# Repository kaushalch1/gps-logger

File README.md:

# gps Logger

## About the Project

this is a gps device designed to record and track journeys without depending on a phone or a constant bluetooth connection.the idea behind this project is to make it easier to collect travel and movement data while hiking or cycling or exploring new places.

the device uses an esp-s3 as its main controller, along with a gps receiver and an oled display, a motion sensor, and a microsd card for storing data. it records information locally so that it can be accessed later, even without an internet connection.

## Tools used

kicad ,github
## how to build it
Step 1 — Solder passive components
Step 2 — Install the ESP32-S3
Step 3 — Install the GPS module
Step 4 — Install the OLED and IMU
Step 5 — Install the microSD socket and controls
Step 6 — Complete power circuitry
St3ep 7-Flash your firmware
## How It Works

When the pcb starts, it initializes the display, gps receiver, microSD card, motion sensor, and bluetooth. The display provides an overview of the device's current status.

When recording starts, the device creates a csv file on the microsd card. It periodically saves available gps information and motion sensor readings to that file.

Bluetooth allows commands to be sent to the device and recorded logs to be requested and since the data is stored locally, recording does not require an active bluetooth connection.
## Features

- GPS Tracking: Collects location, speed, altitude, and time information from the GPS receiver.
- offline logging: Saves gps and sensor readings to a microsd card in csv format without needing a phone or Bluetooth connection.
- OLED display: shows gps status, speed, battery voltage, and recording status.
- Motion sensing: Uses the bmi270 accelerometer and gyroscope to collect movement data.
- Bluetooth connectivity: allows a compatible phone or computer to communicate with the device and request recorded logs.
- Physical controls: includes buttons for starting or stopping recordings and marking waypoints, and switching display pages.
- Status indicators: Uses an led and buzzer to provide basic feedback during operation.
# GPS Logger — Bill of Materials

| Name | Purpose | Quantity | Total Cost (USD) | Link | Distributor |
|---|---|---:|---:|---|---|
| ESP32-S3-WROOM-1-N16R8 | Main MCU (Wi-Fi/BLE) | 1 | 5.54 | [Link](https://www.lcsc.com/product-detail/C2913202.html) | LCSC |
| NEO-M9N-00B | GNSS receiver | 1 | 16.41 | [Link](https://www.lcsc.com/product-detail/C5119087.html) | LCSC |
| BQ24074RGTR | Li-ion battery charger / power path | 1 | 1.59 | [Link](https://www.lcsc.com/product-detail/C54313.html) | LCSC |
| AP2112K-3.3TRG1 | 3.3V LDO regulator | 1 | 0.13 | [Link](https://www.lcsc.com/product-detail/C51118.html) | LCSC |
| USBLC6-2SC6 | USB ESD protection | 1 | 0.13 | [Link](https://www.lcsc.com/product-detail/C7519.html) | LCSC |
| BMI270 | IMU (accelerometer/gyro) | 1 | 1.84 | [Link](https://www.lcsc.com/product-detail/C2836813.html) | LCSC |
| 0.91 inch OLED (ER-OLEDM0.91-1W-I2C) | Display | 1 | 2.80 | [Link](https://www.buydisplay.com/i2c-white-0-91-inch-oled-display-module-128x32-arduino-raspberry-pi) | BuyDisplay |
| USB-C receptacle (TYPE-C-31-M-12) | USB-C charging and data port | 1 | 0.19 | [Link](https://www.lcsc.com/product-detail/C165948.html) | LCSC |
| microSD socket (DM3AT-SF-PEJM5) | Data logging storage | 1 | 1.12 | [Link](https://www.lcsc.com/product-detail/C114218.html) | LCSC |
| JST PH 2-pin header (B2B-PH-K-S) | Battery connector | 1 | 0.03 | [Link](https://www.lcsc.com/product-detail/C131337.html) | LCSC |
| U.FL connector (U.FL-R-SMT-1) | GNSS antenna connector | 1 | 0.19 | [Link](https://www.lcsc.com/product-detail/C88373.html) | LCSC |
| Tact switch (PTS645SM43SMTR92LFS) | User buttons | 5 | 2.04 | [Link](https://www.lcsc.com/product-detail/C221880.html) | LCSC |
| Buzzer 12x9.5mm THT | Audible alerts | 1 | 1.00 | [Link](https://www.lcsc.com/category/51.html) | LCSC |
| 2N3904 | Buzzer driver transistor | 1 | 0.01 | [Link](https://www.lcsc.com/product-detail/C118538.html) | LCSC |
| 1N4148 (DO-35) | Signal/protection diode | 1 | 0.01 | [Link](https://www.lcsc.com/product-detail/C85057.html) | LCSC |
| LED 0805 (red) | Status LED | 1 | 0.01 | [Link](https://www.lcsc.com/product-detail/C84256.html) | LCSC |
| 27nH inductor 0805 | RF matching inductor | 1 | 0.09 | [Link](https://www.lcsc.com/product-detail/C251825.html) | LCSC |
| 10uF capacitor 0805 | Bulk/decoupling capacitors | 6 | 0.29 | [Link](https://www.lcsc.com/product-detail/C15850.html) | LCSC |
| 1uF capacitor 0805 | Filter capacitor | 1 | 0.01 | [Link](https://www.lcsc.com/search?q=CL21B105KBFNNNE) | LCSC |
| 100nF capacitor 0805 | IC bypass capacitors | 4 | 0.03 | [Link](https://www.lcsc.com/product-detail/C1711.html) | LCSC |
| 47pF capacitor 0805 | Filter capacitor | 1 | 0.01 | [Link](https://www.lcsc.com/search?q=0805+47pF+C0G) | LCSC |
| Resistors 0805 (10k, 5k, 1.5k, 1.8k, 100k, 2.1k, 4.7k, 1k) | Pull-ups, LED and divider resistors | 14 | 0.06 | [Link](https://www.lcsc.com/search?q=0805+1%25+resistor) | LCSC |
| PCB (bare boards) | Main PCBs | 1 | 0.40 | [Link](https://jlcpcb.com/) | JLCPCB |
| PCB assembly (PCBA fees) | SMT + through-hole assembly fees | 1 | 7.96 | [Link](https://jlcpcb.com/) | JLCPCB |

**Total estimated cost: USD 41.89**

# schematic

# pcb

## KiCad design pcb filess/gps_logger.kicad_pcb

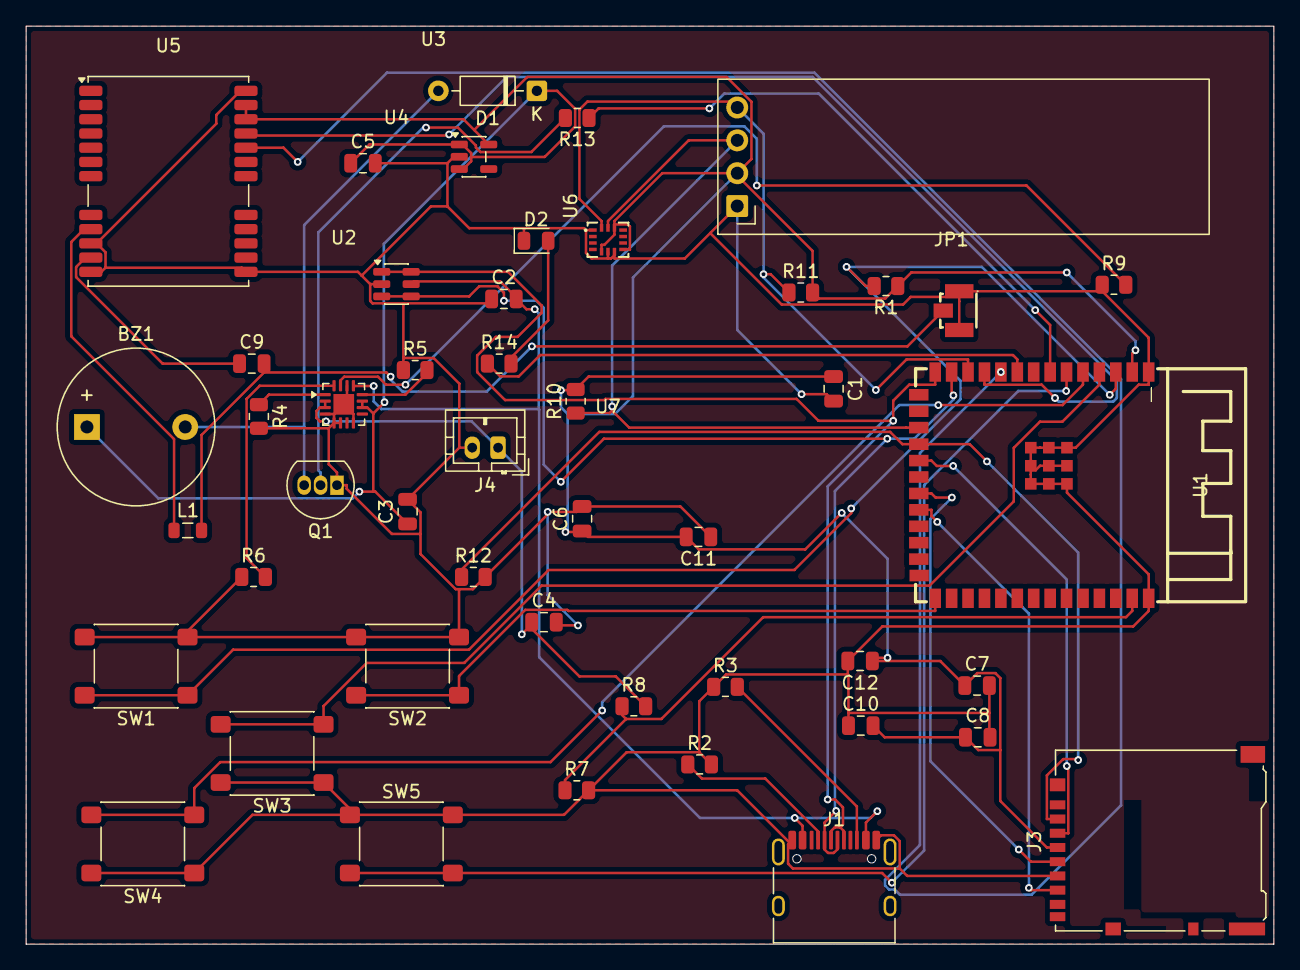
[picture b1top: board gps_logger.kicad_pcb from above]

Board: 2 copper layers, 96.5 x 71.0 mm, 47 parts (0 on the bottom side), 35 nets.

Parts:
BZ1: Buzzer; Buzzer_12x9.5RM7.6
C1, C3, C4, C5, C6, C8: 10uF; C_0805_2012Metric
C2: 1uF; C_0805_2012Metric
C7, C10, C11, C12: 100nF; C_0805_2012Metric
C9: 47pF; C_0805_2012Metric
D1: 1N4148; D_DO-35_SOD27_P7.62mm_Horizontal
D2: LED; LED_0805_2012Metric
J1: USB_C_Receptacle_USB2.0_16P; USB_C_Receptacle_HRO_TYPE-C-31-M-12
J3: Micro_SD_Card; microSD_HC_Hirose_DM3AT-SF-PEJM5
J4: Conn_01x02_Pin; JST_PH_B2B-PH-K_1x02_P2.00mm_Vertical
JP1: U.FL-R-SMT-1; ANT-SMD_UFL-R-SMT-1-10
L1: 27nH; L_0805_2012Metric
Q1: 2N3904; TO-92_Inline
R1, R4, R12: 10k; R_0805_2012Metric
R2, R3: 5k; R_0805_2012Metric
R5: 1.5k; R_0805_2012Metric
R6: 1.8k; R_0805_2012Metric
R7, R8: 100k; R_0805_2012Metric
R9: 2.1k; R_0805_2012Metric
R10, R11: 4.7k; R_0805_2012Metric
R13, R14: 1k; R_0805_2012Metric
SW1, SW2, SW3, SW4, SW5: SW_Push; SW_SPST_PTS645Sx43SMTR92
U1: ESP32-S3-WROOM-1; WIRELM-SMD_ESP32-S3-WROOM-1
U2: BQ24074RGT; VQFN-16-1EP_3x3mm_P0.5mm_EP1.6x1.6mm
U3: AP2112K-3.3; SOT-23-5
U4: USBLC6-2SC6; SOT-23-6
U5: NEO-M9N; ublox_NEO
U6: ER_OLEDM0.91_1x-I2C
U7: BMI270; LGA-14_L3.0-W2.5-P0.50-BR

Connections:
+3V3: C1.1, C6.1, C7.1, C8.1, C10.2, C11.2, C12.1, J3.4 (VDD), R1.1, R10.2, R11.2, U1.2 (3V3), U3.5 (VOUT), U5.22 (V_BCKP), U5.23 (VCC), U6.2 (VCC), U7.5 (VDDIO), U7.8 (VDD), U7.12 (CSB)
+5V: C2.2, J1.A4 (VBUS), J1.A9 (VBUS), J1.B4 (VBUS), J1.B9 (VBUS), U2.13 (IN), U4.5 (VBUS)
/BAT+: C4.1, J4.1, R8.2, U2.2 (BAT), U2.3 (BAT)
/GPIO7: R13.1, U1.7 (IO7)
/GPIO8: R11.1, U1.12 (IO8), U6.4 (SDA), U7.14 (SDX)
/GPIO9: R10.1, U1.17 (IO9), U6.3 (SCL), U7.13 (SCX)
/GPIO10: J3.2 (DAT3/CD), R12.1, U1.18 (IO10)
/GPIO11: J3.3 (CMD), U1.19 (IO11)
/GPIO13: J3.5 (CLK), U1.21 (IO13)
/GPIO14: J3.7 (DAT0), U1.22 (IO14)
/GPIO19: J1.A7 (D-), J1.B7 (D-), U1.13 (IO19), U4.3 (I/O2), U4.4 (I/O2)
/GPIO20: J1.A6 (D+), J1.B6 (D+), U1.14 (IO20), U4.1 (I/O1), U4.6 (I/O1)
/GPS_RX: U1.11 (IO18), U5.21 (RXD/SPI_MOSI)
/GPS_TX: U1.10 (IO17), U5.20 (TXD/SPI_MISO)
/SYS_PWR: BZ1.1 (+), C3.1, C5.1, D1.1 (K), U2.10 (OUT), U2.11 (OUT), U3.1 (VIN), U3.3 (EN)
GND: C1.2, C2.1, C3.2, C4.2, C5.2, C6.2, C7.2, C8.2, C10.1, C11.1, C12.2, D2.1 (K), J1.A1 (GND), J1.A12 (GND), J1.B1 (GND), J1.B12 (GND), J3.6 (VSS), J4.2, JP1.1 (GND), JP1.3 (GND), Q1.1 (E), R2.2, R3.1, R4.2, R5.1, R6.1, R7.2, R9.1, R12.2, SW1.2, SW2.2, SW3.1, SW4.1, SW5.1, U1.1 (GND), U1.40 (GND), U1.41 (GND), U2.4 (~CE), U2.5 (EN2), U2.6 (EN1), U2.8 (VSS), U2.14 (TMR), U2.17 (VSS), U3.2 (GND), U4.2 (GND), U5.10 (GND), U5.12 (GND), U5.13 (GND), U5.24 (GND), U6.1 (GND), U7.1 (SDO), U7.6 (GNDIO), U7.7 (GND)
unnamed: BZ1.2 (-), D1.2 (A), Q1.3 (C)
unnamed: D2.2 (A), R14.2
unnamed: J1.A5 (CC1), R2.1
unnamed: J1.B5 (CC2), R3.2
unnamed: C9.2, JP1.2 (SIN), L1.2
unnamed: Q1.2 (B), R13.2
unnamed: R1.2, SW1.1, U1.3 (EN)
unnamed: SW2.1, U1.27 (IO0)
unnamed: R7.1, R8.1, U1.39 (IO1)
unnamed: SW3.2, U1.4 (IO4)
unnamed: SW4.2, U1.5 (IO5)
unnamed: SW5.2, U1.6 (IO6)
unnamed: R14.1, U1.9 (IO16)
unnamed: R5.2, U2.12 (ILIM)
unnamed: R6.2, U2.16 (ISET)
unnamed: R9.2, U2.15 (ITERM)
unnamed: R4.1, U2.1 (TS)
unnamed: C9.1, U5.11 (RF_IN)
unnamed: L1.1, U5.9 (VCC_RF)

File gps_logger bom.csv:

Reference,Qty / board,Value,Footprint,Part used (MPN),Supplier #,Unit price ($),Price basis,Ext. / board ($),Ext. all boards ($),Confidence,
BZ1,1,Buzzer,Buzzer_Beeper:Buzzer_12x9.5RM7.6,THT magnetic buzzer D12xL9.5 (MPN not in BOM),(LCSC category),$1.0000,LCSC category listing $0.93-$1.11,$1.0000,$5.00,Low,
"C1,C3,C4,C5,C6,C8",6,10uF,C_0805,Samsung CL21A106KAYNNNE 10uF 25V X5R,LCSC C15850,$0.0477,20+ tier (JLCPCB shows $0.0215 @1+),$0.2862,$1.43,High,
C2,1,1uF,C_0805,0805 1uF X7R/X5R MLCC,(basic part),$0.0120,"Typical 0805 1uF price, 50+",$0.0120,$0.06,Low,
"C7,C10,C11,C12",4,100nF,C_0805,Samsung CL21B104KBCNNNC 100nF 50V X7R,LCSC C1711,$0.0063,50+ tier,$0.0252,$0.13,High,
C9,1,47pF,C_0805,0805 47pF C0G MLCC,(basic part),$0.0090,"Typical 0805 C0G price, 50+",$0.0090,$0.05,Low,
D1,1,1N4148,D_DO-35 THT,Changzhou Starsea 1N4148 DO-35,LCSC C85057,$0.0124,50+ tier,$0.0124,$0.06,High,
D2,1,LED,LED_0805,Nationstar NCD0805R1 (red),LCSC C84256,$0.0133,50+ tier,$0.0133,$0.07,Medium,
J1,1,USB_C_Receptacle_USB2.0_16P,USB_C_HRO_TYPE-C-31-M-12,Korean Hroparts TYPE-C-31-M-12,LCSC C165948,$0.1857,5+ tier,$0.1857,$0.93,High,
J3,1,Micro_SD_Card,microSD_HC_Hirose_DM3AT-SF-PEJM5,Hirose DM3AT-SF-PEJM5,LCSC C114218,$1.1151,1+ tier (10+ $0.9573),$1.1151,$5.58,Medium,
J4,1,Conn_01x02_Pin,JST_PH_B2B-PH-K_1x02,JST B2B-PH-K-S(LF)(SN),LCSC C131337,$0.0333,20+ tier,$0.0333,$0.17,High,
JP1,1,U.FL-R-SMT-1,UFL-R-SMT-1-10,HRS U.FL-R-SMT-1(10),LCSC C88373,$0.1939,5+ tier,$0.1939,$0.97,High,
L1,1,27nH,L_0805,EMTEK HSC0805-27NJ-T,LCSC C251825,$0.0893,5+ tier,$0.0893,$0.45,Medium,
Q1,1,2N3904,TO-92,ST(Semtech) 2N3904,LCSC C118538,$0.0149,50+ tier,$0.0149,$0.07,High,
"R1,R4,R12",3,10k,R_0805,0805 1% thick-film,(basic part),$0.0041,100+ tier of same-class Yageo 0805 1%,$0.0123,$0.06,Low,
"R2,R3",2,5k,R_0805,0805 1% thick-film,(basic part),$0.0041,same,$0.0082,$0.04,Low,
R5,1,1.5k,R_0805,0805 1% thick-film,(basic part),$0.0041,same,$0.0041,$0.02,Low,
R6,1,1.8k,R_0805,0805 1% thick-film,(basic part),$0.0041,same,$0.0041,$0.02,Low,
"R7,R8",2,100k,R_0805,0805 1% thick-film,(basic part),$0.0041,same,$0.0082,$0.04,Low,
R9,1,2.1k,R_0805,0805 1% thick-film,(basic part),$0.0041,same,$0.0041,$0.02,Low,
"R10,R11",2,4.7k,R_0805,0805 1% thick-film,(basic part),$0.0041,same,$0.0082,$0.04,Low,
"R13,R14",2,1k,R_0805,0805 1% thick-film,(basic part),$0.0041,same,$0.0082,$0.04,Low,
SW1-SW5,5,SW_Push,SW_SPST_PTS645Sx43SMTR92,C&K PTS645SM43SMTR92LFS,LCSC C221880,$0.4082,10+ tier,$2.0410,$10.21,Medium,
U1,1,ESP32-S3-WROOM-1,WIRELM-SMD_ESP32-S3-WROOM-1,Espressif ESP32-S3-WROOM-1-N16R8,LCSC C2913202,$5.5356,1+ tier (10+ $4.9139),$5.5356,$27.68,High,
U2,1,BQ24074RGT,VQFN-16-1EP_3x3mm,TI BQ24074RGTR,LCSC C54313,$1.5891,1+ tier (10+ $1.3859),$1.5891,$7.95,High,
U3,1,AP2112K-3.3,SOT-23-5,Diodes AP2112K-3.3TRG1,LCSC C51118,$0.1305,5+ tier,$0.1305,$0.65,High,
U4,1,USBLC6-2SC6,SOT-23-6,ST USBLC6-2SC6,LCSC C7519,$0.1283,5+ tier (another mirror $0.1069),$0.1283,$0.64,High,
U5,1,NEO-M9N,RF_GPS:ublox_NEO,u-blox NEO-M9N-00B,LCSC C5119087,$16.4146,"qty-1 price via Flux listing; Mouser $15.68, Digi-Key $27",$16.4146,$82.07,Medium,
U6,1,ER_OLEDM0.91_1x-I2C,Display:ER_OLEDM0.91_1x-I2C,BuyDisplay ER-OLEDM0.91-1W-I2C (white assumed),buydisplay.com,$2.8000,1 pc (10+ $2.73),$2.8000,$14.00,Medium,
U7,1,BMI270,LGA-14_L3.0-W2.5,Bosch BMI270,LCSC C2836813,$1.8389,1+ tier (mirrors $1.80-$1.84),$1.8389,$9.19,High,
,,,,,,,,,,,
Components total,,,,,,,,$33.53,$167.63,,
PCB fabrication,,,,,,,,$0.40,$2.00,,
PCBA assembly fees,,,,,,,,$7.96,$39.79,,
GRAND TOTAL (excl. shipping & tax),,,,,,,,$41.88,$209.42,,
Boards in this estimate,,,,,,,,,5,,
Cost per assembled board,,,,,,,,,$41.88,,
,,,,,,,,,,,
,,,,,,,,,,,
